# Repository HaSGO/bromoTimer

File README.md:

bromoTimer
==========

A timer circuit for a bromograph

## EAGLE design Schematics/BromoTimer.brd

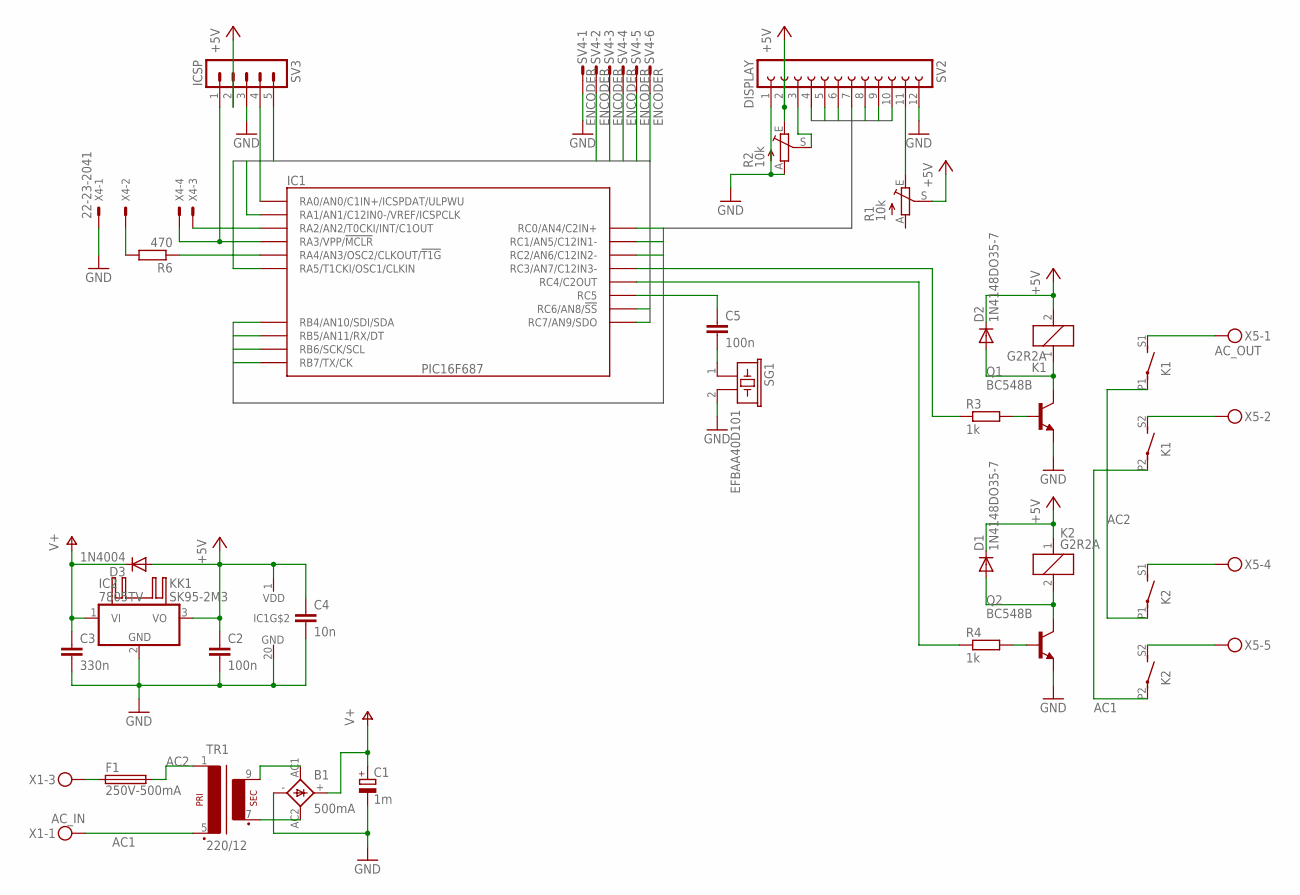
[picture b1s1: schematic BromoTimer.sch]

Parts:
B1: 500mA; 2KBB-R
C1: 1m; E5-13
C2: 100n; C025-024X044
C3: 330n; C050-050X075
C4: 10n; C025-024X044
C5: 100n; C075-032X103
D1, D2: 1N4148DO35-7; DO35-7
D3: 1N4004; DO41-10
F1: 250V-500mA; SH22
IC1: PIC16F687; DIP20
IC2: 7805TV; TO220V
K1, K2: G2R2A; MPN G2R-2A-DC24
KK1: SK95-2M3
Q1, Q2: BC548B; TO92-EBC
R1, R2: 10k; CA6V
R3, R4: 1k; 0207/7
R6: 470; 0207/7
SG1: EFBAA40D101
SV2: DISPLAY; FE12
SV3: ICSP; MA05-1
SV4: ENCODER; L06P
TR1: 220/12; EI30-1
X1: AC_IN; MKDSN1,5/3-5,08
X4: 22-23-2041
X5: AC_OUT; MKDSN1,5/5-5,08

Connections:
+5V: C2.1, C4.1, D1.C, D2.C, D3.A, IC1.1 (VDD), IC2.3 (VO), K1.2, K2.1, R1.S, R2.E, SV2.2, SV3.2
A: IC1.19 (RA0/AN0/C1IN+/ICSPDAT/ULPWU), SV3.4, SV4.5
AC1: K1.P2, K2.P2, TR1.5 (P2), X1.1
AC2: F1.2, K1.P1, K2.P1, TR1.1
B: IC1.18 (RA1/AN1/C12IN0-/VREF/ICSPCLK), SV3.5, SV4.6
B0: IC1.13 (RB4/AN10/SDI/SDA), SV2.7
B1: IC1.12 (RB5/AN11/RX/DT), SV2.8
B2: IC1.11 (RB6/SCK/SCL), SV2.9
B3: IC1.10 (RB7/TX/CK), SV2.10
EN: IC1.16 (RC0/AN4/C2IN+), SV2.6
GND: B1.-, C1.-, C2.2, C3.2, C4.2, IC1.20 (GND), IC2.2 (GND), Q1.E, Q2.E, R2.A, SG1.2, SV2.1, SV2.12, SV3.3, SV4.1, X4.1
LG: IC1.9 (RC7/AN9/SDO), SV4.2
LR: IC1.8 (RC6/AN8/!SS), SV4.3
unnamed: R1.E, SV2.11
unnamed: B1.AC2, TR1.7 (S3)
unnamed: R2.S, SV2.3
unnamed: Q2.B, R4.2
unnamed: Q1.B, R3.2
unnamed: D1.A, K2.2, Q2.C
unnamed: D2.A, K1.1, Q1.C
unnamed: K1.S1 (S), X5.1
unnamed: K1.S2 (S), X5.2
unnamed: K2.S1 (S), X5.4
unnamed: K2.S2 (S), X5.5
unnamed: B1.AC1, TR1.9 (S4)
unnamed: IC1.17 (RA2/AN2/T0CKI/INT/C1OUT), X4.3
unnamed: IC1.6 (RC4/C2OUT), R4.1
unnamed: IC1.4 (RA3/VPP/!MCLR), SV3.1, X4.4
unnamed: IC1.7 (RC3/AN7/C12IN3-), R3.1
unnamed: C5.1, IC1.5 (RC5)
unnamed: C5.2, SG1.1
unnamed: IC1.3 (RA4/AN3/OSC2/CLKOUT/!T1G), R6.1
unnamed: R6.2, X4.2
unnamed: F1.1, X1.3
RS: IC1.15 (RC1/AN5/C12IN1-), SV2.4
RW: IC1.14 (RC2/AN6/C12IN2-), SV2.5
SW: IC1.2 (RA5/T1CKI/OSC1/CLKIN), SV4.4
V+: B1.+, C1.+, C3.1, D3.C, IC2.1 (VI)

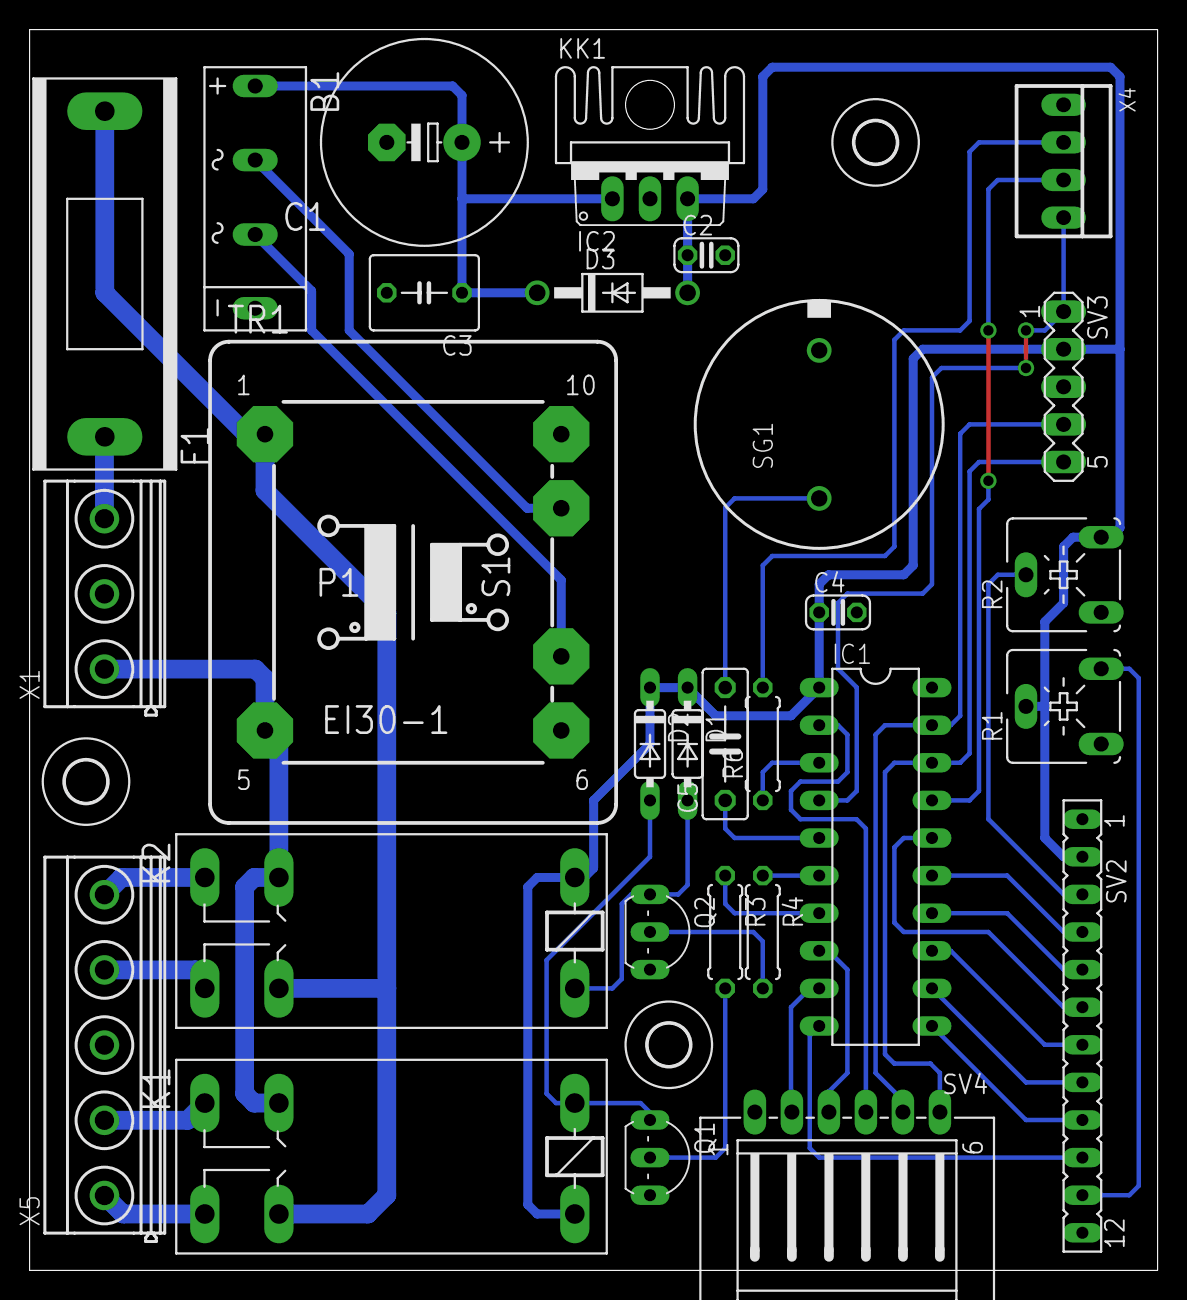
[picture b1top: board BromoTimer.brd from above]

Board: 2 copper layers, 76.2 x 83.8 mm, 33 parts (0 on the bottom side), 38 nets.

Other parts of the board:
U$2, U$3, U$4: 2,8

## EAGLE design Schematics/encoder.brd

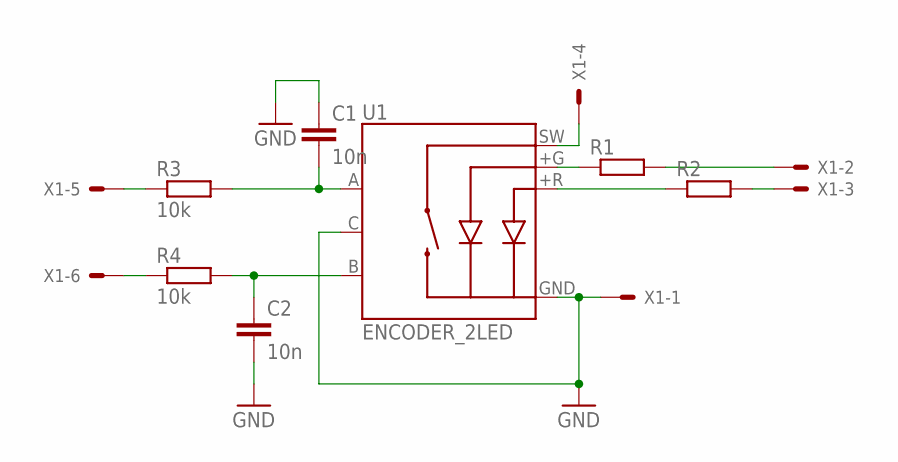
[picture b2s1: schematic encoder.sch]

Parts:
C1, C2: 10n; C025-024X044
R1, R2: R-EU_R0603; R0603
R3, R4: 10k; R0603
U1: ENCODER_2LED; ENCODER_LED_2
X1: 22-23-2061

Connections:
GND: C1.1, C2.2, U1.C, U1.GND (-), X1.1
unnamed: R1.2, X1.2
unnamed: R2.2, X1.3
unnamed: R1.1, U1.+G
unnamed: U1.SW, X1.4
unnamed: C1.2, R3.2, U1.A
unnamed: C2.1, R4.2, U1.B
unnamed: R2.1, U1.+R
unnamed: R4.1, X1.6
unnamed: R3.1, X1.5

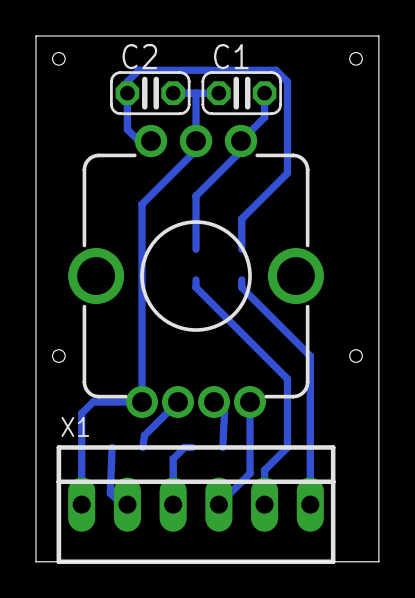
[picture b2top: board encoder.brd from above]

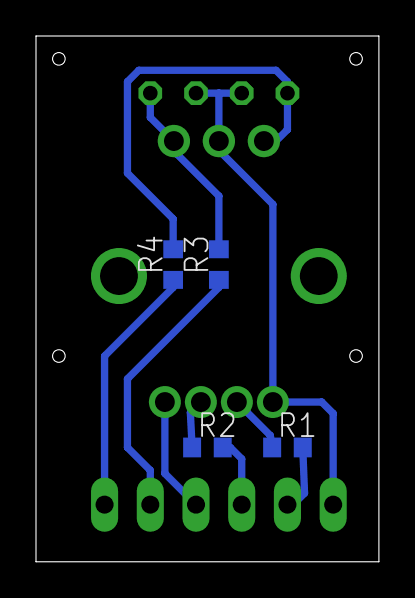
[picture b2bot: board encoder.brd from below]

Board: 2 copper layers, 19.1 x 29.2 mm, 8 parts (4 on the bottom side), 10 nets.

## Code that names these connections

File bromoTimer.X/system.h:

#ifndef SYSTEM_H
#define SYSTEM_H
/******************************************************************************/
/* System Level #define Macros                                                */
/******************************************************************************/

/* Encoder */
/* Segnali quadratura encoder */
#define ENC_A RA0
#define ENC_B RA1
/* Pulsante encoder */
#define ENC_SW RA5
/* LED Rosso */
#define ENC_LR RC6
/* LED Verde */
#define ENC_LG RC7

/* Comandi frontalino */
/* Pulsante di accensione esterno */
#define EXT_SW RA2
/* Led esterno */
#define EXT_LED RA4

/* Sensore stato coperchio */
#define EXT_LID RA3

/* Comando buzzer */
#define BUZZER RC5

/* Comandi display LCD */
/* Display enable */
#define DISPLAY_EN RC0
/* Display register select */
#define DISPLAY_RS RC1
/* Display Read/Write */
#define DISPLAY_RW RC2
#define DISPLAY_B0 RB4
#define DISPLAY_B1 RB5
#define DISPLAY_B2 RB6
#define DISPLAY_B3 RB7

/* Controllo rele lampade */
#define LAMP_1 RC4
#define LAMP_2 RC3

/* Microcontroller MIPs (FCY) */
#define _XTAL_FREQ      1e6L
#define FCY             _XTAL_FREQ/4

/******************************************************************************/
/* System Function Prototypes                                                 */
/******************************************************************************/

/* Custom oscillator configuration funtions, reset source evaluation
functions, and other non-peripheral microcontroller initialization functions
go here. */

void ConfigureOscillator(void); /* Handles clock switching/osc initialization */

void PlayBuzzerMs(uint16_t duration);

void putch(char data);

enum status {
    mode_COUNTDOWN,
    mode_SET,
    mode_NOP
};

volatile enum status status = mode_NOP;

/* System flag variable. The flags are:
 * bit 0: encoder button pressed
 * bit 1: timer1 overflow
 * bit 3: lid opened
 */
volatile uint8_t system_flags = 0;

#define ENCODER_BUTTON_PRESSED	0x01
#define TIMER1_OVERFLOW		0x02
#define LID_OPEN                0x04

#endif

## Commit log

2012-12-02 Add license
2012-12-02 Initial commit
    Schematic is nearly done; still have to check dimensions and lay out the board.
2012-12-02 Ignore EAGLE backup files
2012-12-02 Ignore EAGLE board backups
2012-12-02 Finished first version of the schematic.
2012-12-02 Add board, initial component placement
    Still have to confirm component size & footprint.
2012-12-03 Initial code release
    Just the default Microchip boilerplate. Will add actual code later. :)
2012-12-08 Fixed bug in schematics
    The poles on the diode bridge were inverted.
2012-12-08 Add gitignore comment
2012-12-08 Use 12V relay.
    Use 12V relay since V relays are not common.
2012-12-08 Add ICSP header
2012-12-08 Add buzzer and diode protection to 7805.
2012-12-08 Add support for external LED
2012-12-09 Add 1n4004 diode
2012-12-09 Fix bug in relay protection
2012-12-09 Add on-board buzzer
2012-12-09 Fixed footprints, added resistor for main led.
2012-12-09 Better connector pinouts
2012-12-12 Add proper footprint for relays
2012-12-12 Initial component layout.
2012-12-12 Fix some ERC errors
    Come traces were not connected on the transformer, R1 and R2 were missing
    values, so was TR1.
2012-12-12 Eye candy changes
    Added a frame for the power circuits, moved the components around to better
    fit the frame.
2012-12-12 Component placement finished
    This is just a candidate though. The area with Q1 Q2 and Q3 could get optimized
    a little more though...
2012-12-12 Adjusted some positions in the board layout
2012-12-12 Relay coil voltage is 5V
2012-12-12 Routing nearly done
2012-12-12 Integrating a fuse in the circuit
    Moved the supply circuit a bit to make room for the fuse holder.
2012-12-12 Routing complete
    Well, nearly... I routed everything but two wires.
2012-12-23 Routing completed, no jumper wires
    Routing fully completed, RDC passing.
2013-01-11 migrate to EAGLE 6.4.0
2013-01-13 Add support for lid state sensor
2013-01-19 Small changes to PCB layout.
2013-01-20 Add board name & version in layout.
2013-01-20 moved R2, R4, R5 and Q3 to better positions.
2013-02-10 Define pin functions.
    Define all pin functions based on circuit.
2013-02-16 Swap functionality of RA3 and RA4
    Internal pullup not available on RA3, but needed for lid sensor.
2013-02-16 Add direction and pull-ups to I/O
2013-03-09 Add encoder PCB
    Added the encoder mini PCB, schematics with the correct footprint.
2013-03-09 Clean up R1
2013-03-09 Use PicKit2 as the programmer
2013-03-09 Move to xc8 instead of hi tecc pic
2013-03-09 Implement sample code
    When programmed, this should toggle the buzzer on and off.
2013-03-10 Correct trimmer footprints
2013-03-10 Add caps to encoder breakout
2013-03-10 Increase default keepout
    Default keepout increased to 25mil. Also, inverted function of RC6 and RC7.
    Change is also made in code to reflect this.
2013-03-10 Using XC8 v1.12
2013-03-18 Complete XC8 transition
    Changed all references to the htc header file.
2013-03-18 Add configuration word
2013-03-18 Configure internal RC oscillator
2013-03-24 Enable global weak pull-ups
2013-03-24 Disable relay and buzzer at boot.
2013-03-24 Enable pull-ups on A & B encoder lines
2013-03-24 Encoder test mode
2013-03-25 Ignore .pro files, better EAGLE ignore
2013-03-25 New PCB prototype
    The new PCB is a little taller and a lot less wide. It has extra space for the
    7805 heatsink. Connector layout should be better, too.
2013-03-25 Final touches
    Mitered the last corners, optimized some tracks, minor changes.
2013-03-26 Change some compiler parameters
2013-04-03 Custom PIC part, minor layout changes
    Schematic:
    - changed encoder connector to right angle type
    - rewired trimmer for LCD contrast, it needs to vary voltage, not resistance
    - add net class for power line, specifying 24thou width and 12thou keepout
    - LCD trimmers are 10k, not 100k
    - add decoupling cap to IC1
2013-04-03 Add current limiting resistors for LEDs
2013-04-03 Add EAGLE description
2013-04-04 Be sure to disable pull-ups on PORTB
    Individual pull-ups are enabled by default if !RABPU is enabled.
2013-04-04 Swap RA3 and RA4 function.
    This was an error, RA3 is input only! So, external led is controlled via RA4
    (there's a current limiting resistor attached to it in the schematics, too) and
    RA3 is the lid sensor input.
2013-04-04 Add comment explaining change in OPTION_REG.
2013-04-06 Use piezo instead of buzzer, add mounting holes
    Use piezo instead of a buzzer so we save a resistor and a transistor. The piezo
    will ring via PWM by the PIC. Re-routed portions of the PCB for a better fit.
    Add mounting holes to PCB.
2013-05-26 Add LCD library.
    Amended to correct some bugs, mainly with an extra enable when sending a byte in
    nibble mode.
2013-05-26 Remove autogenerated files
    This files are autogenerated by MPLAB X.
2013-05-26 Moved pin specifications
    It makes much more sense to store pin specifications in system.h.
2013-05-26 Add routine to play buzzer
    Buzzer type was changed from electromechanical beeper to piezoelectric. For it
    to work, we have to excite it with a 4 kHz square wave.
2013-05-26 Fix small TRISA bug
    RA4 is the only output, not RA3. Also, disable weak pull-up on RA3 since WPU is
    not supported on that pin.
2013-05-26 Small cosmetic changes, add guard on system.h
2013-05-26 Disable analog function on pins
    We discovered this causes trouble with weak pull-ups.
2013-05-26 Add putch() routine
    This enables the use of the printf() function in the standard library.
    Also, initialize the LCD display on application init.
2013-05-26 Disable all LEDs at initialization.
2013-05-26 Add self-test routine
    The self-test routine lights every available LED and clicks both relays to test
    everything.
2013-05-26 Read from encoder
    Enable interrupt-on-change on RA0 and RA1 to read from encoder. Encoder turns
    modify a global counter, which is displayed on the LCD in the main loop.
2013-06-02 Include lcd.h to initialize LCD
2013-06-02 Add define to please MPLAB X
    You have to define __PICCPRO__ in your project in order for the MPLAB X parser
    to not underline __delay* functions.
2013-06-08 putch's parameter is constant.
2013-06-08 Changed all post-increments to pre-increment.
    Pre-increments are more efficient in loops (and in general, too).
2013-06-08 Implementing basic state system
    Just a basic state machine, switches from getting a value and displaying "Menu".
2013-06-17 Enhance selftest mode
    This patch adds a while loop to wait for the user to depress the encoder switch
    before exiting selftest mode and continuing with the program.
2013-06-17 Refactor enc_val to seconds
    This variable will be used to specify the timer seconds. Also, using the
    correct mask for printf.
2013-06-17 Implement basic flag system
    Flags are set according to interrupts to process events synchronously in the
    main loop. This is to keep the ISR short and simple, and to limit the number
    of global variables.
    This patch implements a basic timer system, first the user selects the time and
    on a button press the microcontroller activates both lamps and starts counting
    down. When the timer ends, both lamps are shut down and the system can start
2013-06-17 bromotimer PCB: added low pass filter to encoder
    Added LPF to avoid chattering, added holes to encoder pcb.
2013-06-17 Fix some DRC errors
2013-07-14 BromoTimer board: aligned pots
    Both potentiometers are aligned now. Also, manually approved DRC clearance
    errors between 220V terminal pins.
2013-07-15 Moved the SelfTest routine to user.c
2013-07-15 Enhanced UI a bit
    Added frendlier messages, and do not rewrite whole line in countdown mode, but
    just the seconds. This still has some bugs, namely, then the seconds go from
    hundreds to tens and from tens to ones the trailing digit is not erased.
2014-05-22 Move code to function
2014-05-22 Use more meaningful character to reset LCD character counter
2014-05-22 Enable lid sensing
    This commit enables the timer to stop when lid is opened.
2014-05-22 Whitespace changes
2014-05-22 Use lcd_clear when applicable
2014-05-28 Fix lid bug
    MCLR is connected to the lid sensor, so it can't be used.
2014-05-28 Remember to reset flags
2014-05-28 Use external switch for self test
2014-05-28 Enable pull-up on RA3 pin
    This should definitively fix the lid sensor malfunctioning
2014-05-28 Disable analog functions first
2014-05-28 Light up LED only when we finish self test.
    Also, fix small bug.
2014-05-28 Remove bogus attribute
2014-05-28 Use \n in printf to move to the second half of the LCD

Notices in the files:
parts and their libraries:
SparkFun: Licensing: CC v3.0 Share-Alike You are welcome to use this library for commercial purposes.
